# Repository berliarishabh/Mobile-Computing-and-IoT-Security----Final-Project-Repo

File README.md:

# Mobile-Computing-and-IoT-Security----Final-Project-Repo

#### Motivation:

With the advent of mass-deployed broadband Internet connections and the development of Wireless technologies (BLE, Zigbee etc.), smart connected devices in the home are a very real and practical possibility. 

A Smart Home is one that is designed to deliver or distribute a number of services within and outside the home through a range of networked devices. [Juniper Research]

#### Objective:

To develop a complete Internet of Thing system for a Smart Home such as Samsung SmartThings, Notion etc. This would require us to build individual BLE based Sensor Tags. Every Tag would have a specific sensor to sense parameters such as Temperature, Humidity, Ambient Light, Proximity, Pressure, Touch etc. 
These Tags will be built on the BLE Nano (based on the Nordic nRF51822 SoC). Each individual tag will have the sensor circuit interfaced with the BLE Nano and would run on a single coin-cell battery (CR-2032). We would use the Leopard Gecko EFM32 Board as one of the Tags as well to use the LESENSE sensor. 

The Sensor Tags would connect and transmit data to a small Microcomputer (Raspberry Pi 3) based hub. Since, the Raspberry Pi has Wi-Fi connectivity it enables us to take our data to the cloud, where the data processing would take place. 

We plan to use one of the following platforms to collect, visualize & analyze data and trigger responses accordingly:
•	Sci-kit Learn
•	ThingSpeak
•	Phant
This would allow us to host a web server on Rasp Pi for the User Interface where the User can monitor all the sensor data on Graphs and Issue Override Commands such as GetTemp, GetPressure etc.
If we are able to accomplish this well within our time bounds, we would try to implement an App to give notifications on the Phone.

Also, since we have the sensor data and trigger points we could use to actuate physical things inside your home e.g. Using the Ambient light and Temperature sensor data, a servo motor could be used to actuate your Window Blinds depending on the Light and temperature settings etc. 

There would be 2 set of Commands, Trigger Commands and Override Commands. 
Trigger Commands are sent through the ThingSpeak or Sci-Kit platform depending on the set points. If the sensor data goes above or below a notification would be given. These commands are even used to Actuate something if required.

Override Commands are sent by the user through the UI, these commands are to get the most recent Sensor Data and post it on the Screen.

#### Block Diagram of a System

#### Block Diagram of the System

#### Test Methodology: 

1.	Testing functionality of individual Sensor Tags
  a.	Validate sensor data 
  b.	Testing if sensor tag posts data according to Set Points
  c.	Testing if sensor tag sends data when requested with a command.
2.	Testing the Server
  a.	Test individual sensor connections to the server
  b.	Test the Data Logging and setup Visualization through Graphs.
  c.	Testing the Trigger commands and Override Commands
3.	Integration and Testing
  Integration of the system and testing individual points

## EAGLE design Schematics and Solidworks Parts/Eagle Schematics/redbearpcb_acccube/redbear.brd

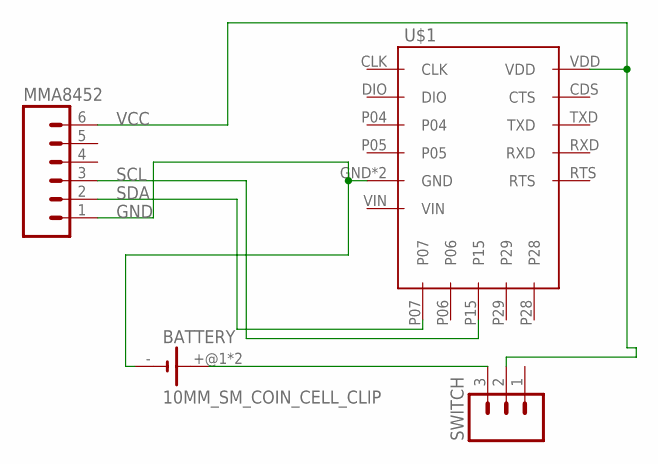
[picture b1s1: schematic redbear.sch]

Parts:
BATTERY: 10MM_SM_COIN_CELL_CLIP
MMA8452: M06NO_SILK_FEMALE_PTH; 1X06_NO_SILK
SWITCH: M03PTH; 1X03
U$1: REDBEAR_NANOBREAKOUT1; BREAKOUT

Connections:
GND: BATTERY.-, MMA8452.1, U$1.GND, U$1.GND1 (GND)
unnamed: BATTERY.+@1 (+), BATTERY.+@2 (+), SWITCH.3
SCL: MMA8452.3, U$1.P15
SDA: MMA8452.2, U$1.P07
VCC: MMA8452.6, SWITCH.2, U$1.VDD

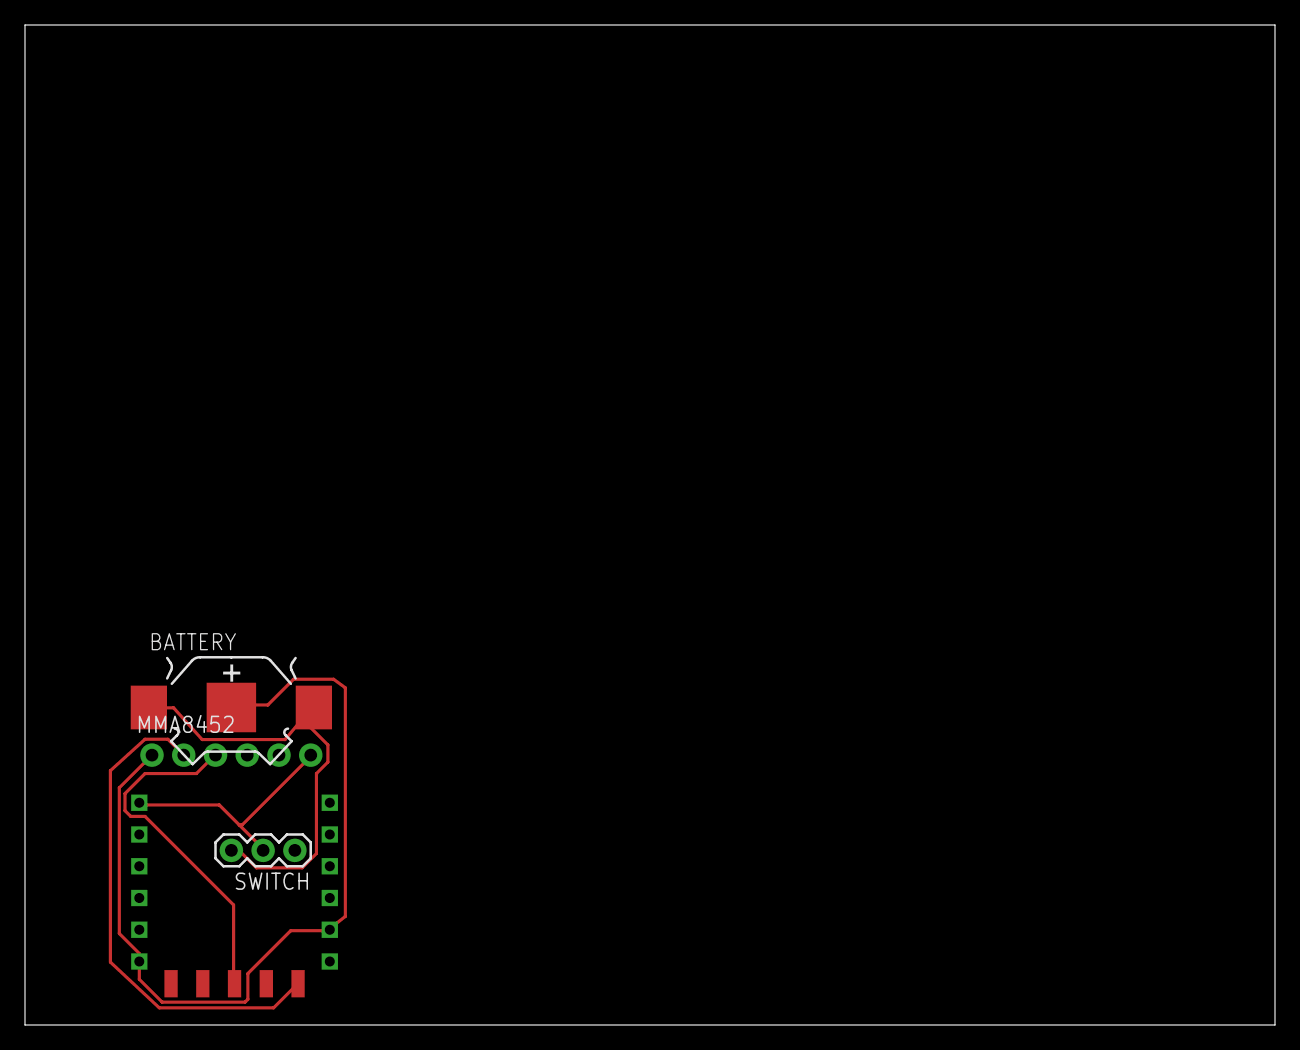
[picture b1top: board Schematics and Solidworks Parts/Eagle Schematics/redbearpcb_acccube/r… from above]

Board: 2 copper layers, 100.0 x 80.0 mm, 4 parts (0 on the bottom side), 5 nets.

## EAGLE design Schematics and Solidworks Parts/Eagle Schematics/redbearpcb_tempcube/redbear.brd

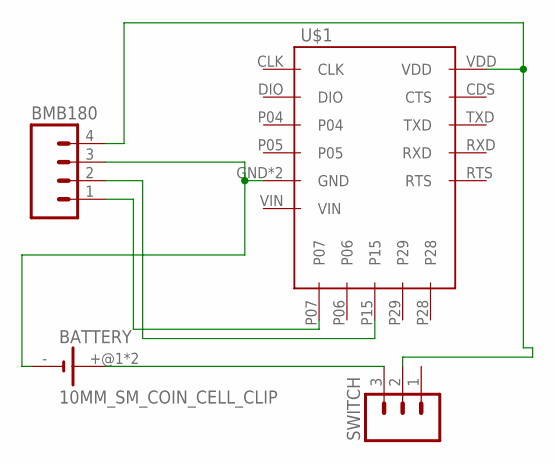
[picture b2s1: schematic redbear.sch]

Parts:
BATTERY: 10MM_SM_COIN_CELL_CLIP
BMB180: M04NO_SILK_ALL_ROUND; 1X04_NO_SILK_ALL_ROUND
SWITCH: M03PTH; 1X03
U$1: REDBEAR_NANOBREAKOUT1; BREAKOUT

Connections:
GND: BATTERY.-, BMB180.3, U$1.GND, U$1.GND1 (GND)
unnamed: BATTERY.+@1 (+), BATTERY.+@2 (+), SWITCH.3
SCL: BMB180.2, U$1.P15
SDA: BMB180.1, U$1.P07
VCC: BMB180.4, SWITCH.2, U$1.VDD

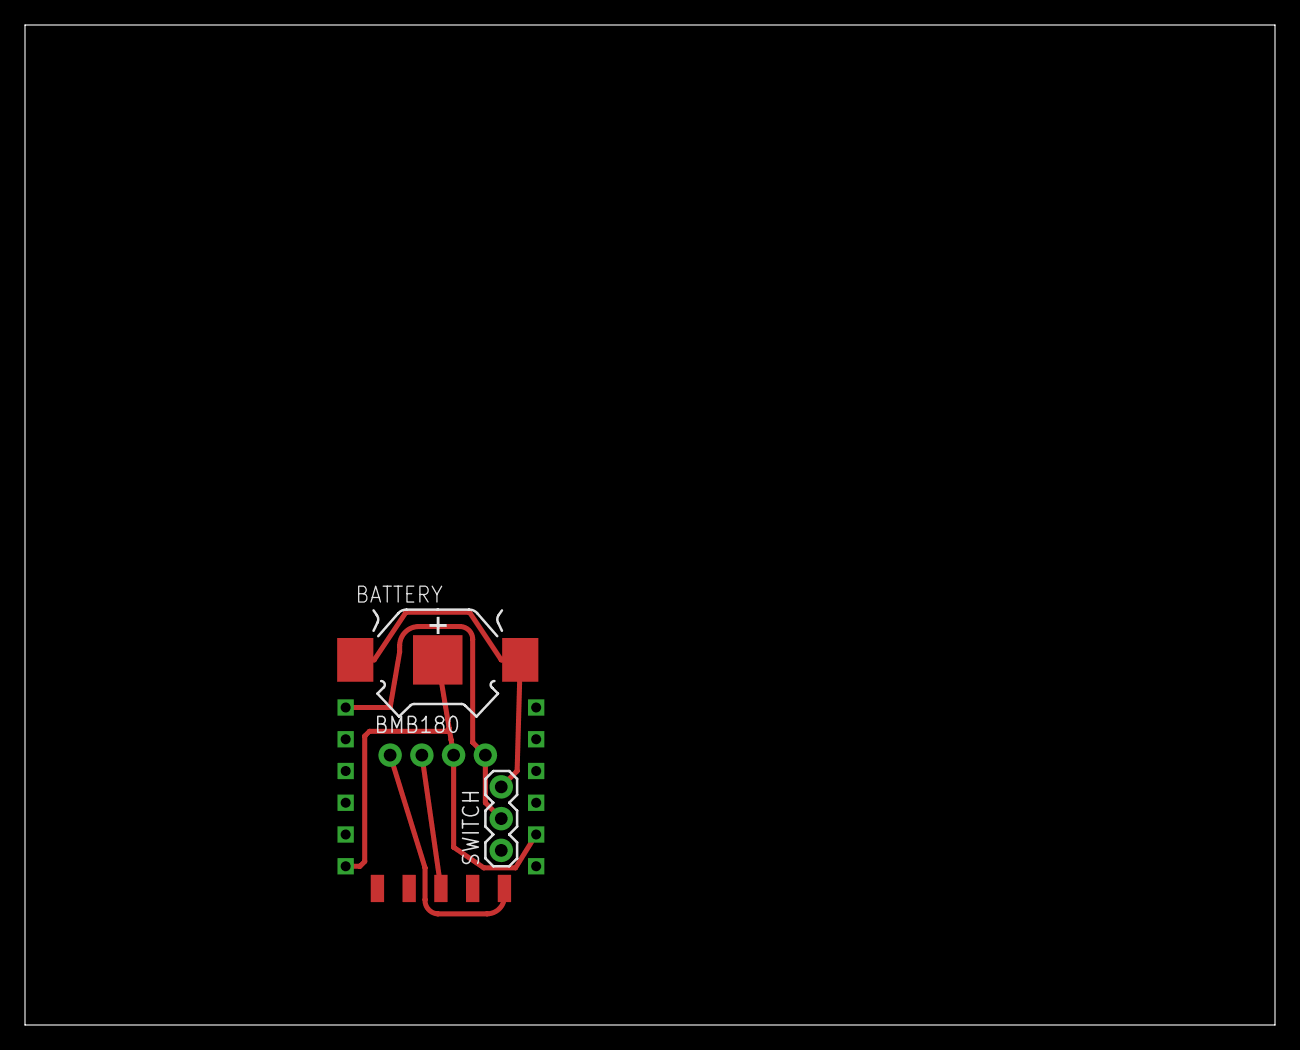
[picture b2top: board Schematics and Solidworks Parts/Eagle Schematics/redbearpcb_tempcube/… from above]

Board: 2 copper layers, 100.0 x 80.0 mm, 4 parts (0 on the bottom side), 5 nets.

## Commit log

2017-03-06 Project Upload

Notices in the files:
parts and their libraries:
SparkFun-Connectors: Licensing: Creative Commons ShareAlike 4.0 International - https://creativecommons.org/licenses/by-sa/4.0
